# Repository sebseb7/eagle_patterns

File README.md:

eagle_patterns
==============

templates

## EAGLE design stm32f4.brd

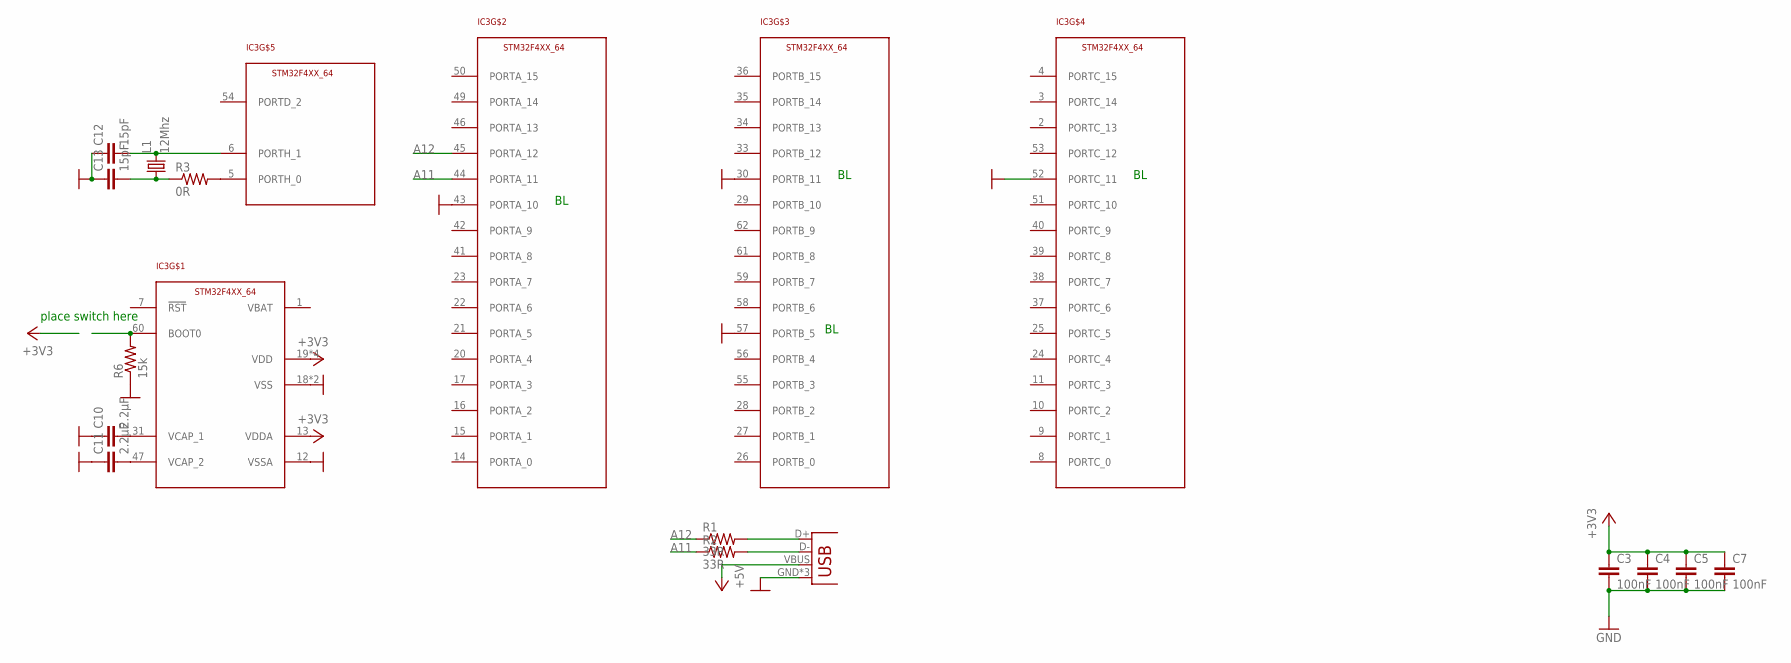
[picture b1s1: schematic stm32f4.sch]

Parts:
C3, C4, C5, C7: 100nF; 0402-CAP
C10, C11: 2.2µF; 0805
C12, C13: 15pF; 0402-CAP
IC3: STM32F4XX_64; TQFP64
JP1: USB-MICROB
L1: 12Mhz; X22
R1, R2: 33R; 0402-RES
R3: 0R; 0402-RES
R6: 15k; 0402-RES

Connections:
+3V3: C3.1, C4.1, C5.1, C7.1, IC3.13 (VDDA), IC3.19 (VDD), IC3.32 (VDD), IC3.48 (VDD), IC3.64 (VDD)
+5V: JP1.VBUS
A11: IC3.44 (PORTA_11), R2.1
A12: IC3.45 (PORTA_12), R1.1
GND: C3.2, C4.2, C5.2, C7.2, C10.1, C11.1, C12.1, C13.1, IC3.12 (VSSA), IC3.18 (VSS), IC3.30 (PORTB_11), IC3.43 (PORTA_10), IC3.52 (PORTC_11), IC3.57 (PORTB_5), IC3.63 (VSS), JP1.GND, JP1.MT1 (GND), JP1.MT2 (GND), R6.1
unnamed: JP1.D-, R2.2
unnamed: JP1.D+, R1.2
unnamed: C10.2, IC3.31 (VCAP_1)
unnamed: C11.2, IC3.47 (VCAP_2)
unnamed: IC3.5 (PORTH_0), R3.2
unnamed: C13.2, L1.1, R3.1
unnamed: C12.2, IC3.6 (PORTH_1), L1.3 (2)
SW1: IC3.60 (BOOT0), R6.2

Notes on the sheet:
place switch here

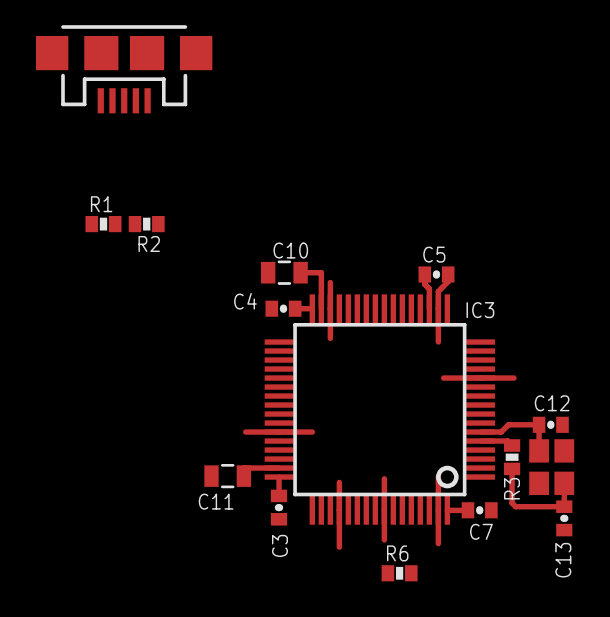
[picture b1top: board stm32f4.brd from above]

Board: 2 copper layers, 15 parts (0 on the bottom side), 12 nets.

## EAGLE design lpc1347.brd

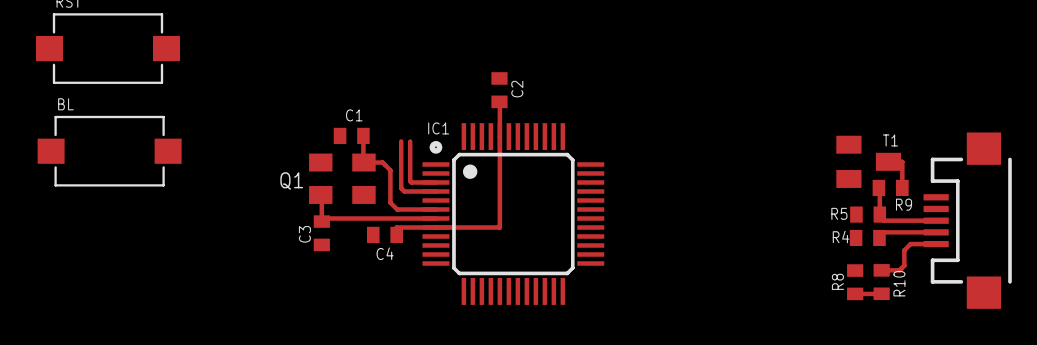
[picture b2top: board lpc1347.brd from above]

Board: 2 copper layers, 15 parts (0 on the bottom side), 14 nets.

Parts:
BL: SWITCH_MCTAEF
C1, C3: 22pF; C0402
C2, C4: 100nF; C0402
IC1: LQFP48
Q1: 12Mhz; MT
R4, R5: 33R; R0402
R8, R10: 15k; R0402
R9: 1k5; R0402
RST: SWITCH_MCTAEF
T1: Si2301DS; SOT23
X1: USB-MICROB

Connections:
01: BL.2, IC1.4
06: IC1.22, T1.1
+3V3: C2.2, C4.2, IC1.8, IC1.44, T1.2
+5V: R10.1, X1.VBUS
GND: BL.1, C1.1, C2.1, C3.1, C4.1, IC1.5, IC1.41, R8.1, RST.1, X1.GND, X1.MT1, X1.MT2
unnamed: C3.2, IC1.7, Q1.1
unnamed: C1.2, IC1.6, Q1.3
unnamed: R5.2, R9.1, X1.D+
unnamed: R4.2, X1.D-
unnamed: IC1.19, R4.1
unnamed: R9.2, T1.3
unnamed: IC1.20, R5.1
RST: IC1.3, RST.2
VBUS: IC1.14, R8.2, R10.2

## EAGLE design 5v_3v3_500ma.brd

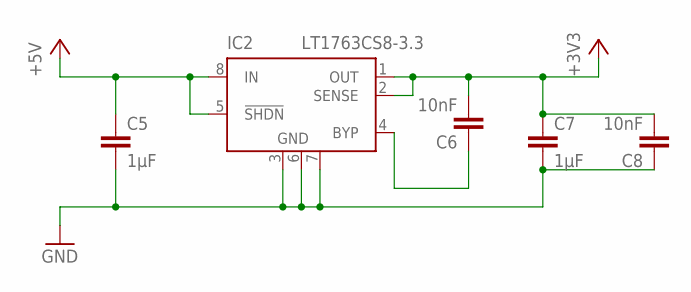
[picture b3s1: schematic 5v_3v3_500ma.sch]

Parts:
C5, C7: 1µF; 0805
C6, C8: 10nF; C0402
IC2: LT1763CS8-3.3; SOIC8

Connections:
+3V3: C6.2, C7.1, C8.2, IC2.1 (OUT), IC2.2 (SENSE)
+5V: C5.1, IC2.5 (!SHDN), IC2.8 (IN)
GND: C5.2, C7.2, C8.1, IC2.3 (GND), IC2.6 (GND), IC2.7 (GND)
unnamed: C6.1, IC2.4 (BYP)

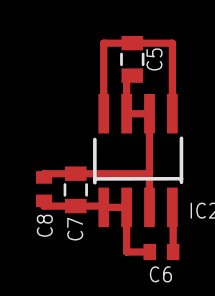
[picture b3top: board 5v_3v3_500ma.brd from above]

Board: 2 copper layers, 5 parts (0 on the bottom side), 4 nets.

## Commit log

2012-10-24 lpc1347 & lt1763 pattern
2012-10-24 added brd for lt1763
2012-10-24 added brd for lpc1347
2013-02-04 stm32f3 pattern

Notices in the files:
parts and their libraries:
SparkFun-Connectors: Licensing: CC v3.0 Share-Alike You are welcome to use this library for commercial purposes.
